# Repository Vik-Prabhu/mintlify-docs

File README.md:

# Smart Fault Detector

## Project Description

The **Smart-Fault-Detector** is a specialized diagnostic device engineered to detect actuator faults and failures in high-stakes systems like rockets and robotics. By monitoring the "pulse" of an actuator through electrical and mechanical sensors, it identifies anomalies before they lead to catastrophic system failure.

## 📘 Project Documentation & Deployment

### 🌐 Documentation (Mintlify)

This project uses **Mintlify** to host clean, modern documentation.

- Built using MDX
- Supports images, code blocks, and downloadable assets
- Automatically deployed on every update

**Documentation URL:**  https://teamrobomanipal-3a657712.mintlify.app/Introduction

````
To run docs locally:
npm install
mintlify dev
````

---

### 🚀 Backend Deployment (Render + Flask)

The backend is a **Flask + Socket.IO** server deployed on **Render**.

#### Why Render?

- Free tier support
- Simple GitHub integration
- Works well with Flask APIs
- Public endpoint accessible by ESP devices

#### Tech Stack

- Python
- Flask
- Flask-SocketIO
- Eventlet
- Render Web Service

#### Deployment Flow

1. Push code to GitHub
2. Create a **Web Service** on Render
3. Render installs dependencies from `requirements.txt`
4. App runs on a public HTTPS URL

 **Dashboard URL:** https://mintlify-docs-w26p.onrender.com

---

### 📡 ESP ↔ Server Communication

- ESP device sends data via HTTP / Socket.IO

- Flask server receives and processes data

- Real-time updates supported using WebSockets
- Designed for low-latency actuator/health monitoring

---

### 📂 Key Files

```text
.
├── Firmware            # Contains ESP32-C3 Code
├── PCB                 # KiCAD Design Files
```

```
.
├── docs.json             # Contains structured metadata for the project 
├── package-lock.json     # Auto-generated file for mintlify
```

```
Dashboard_src
├── server.py              # Webserver UI
├── health_model.py        # Predictive Algorithm
├── requirements.txt       # Python dependencies
```

---

### 🛠️ requirements.txt

```txt
flask
flask-socketio
eventlet
```

---

### ✅ Status

- [x] Backend deployed on Render
- [x] Documentation live on Mintlify
- [x] ESP integration working

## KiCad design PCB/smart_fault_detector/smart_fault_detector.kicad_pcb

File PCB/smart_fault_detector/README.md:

# Hardware-Hackathon-2.0
for hackathon

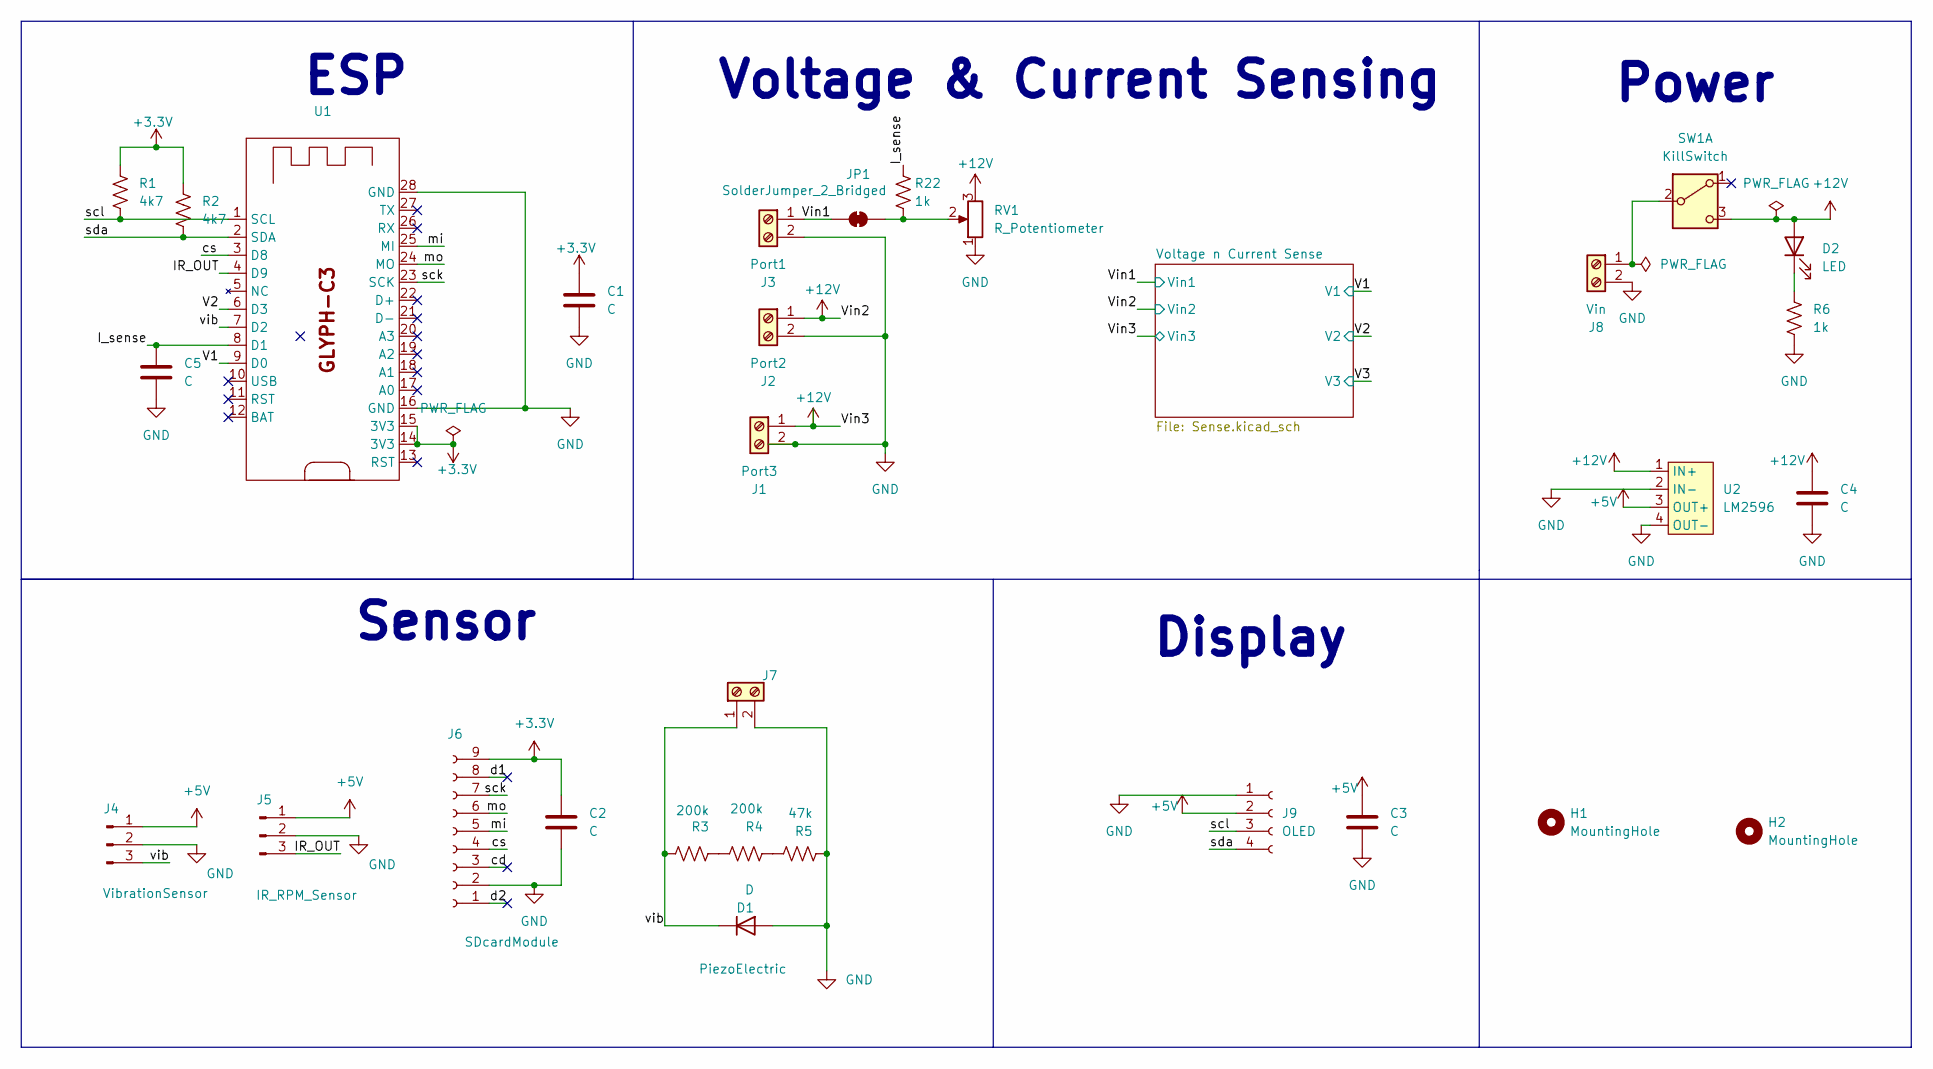
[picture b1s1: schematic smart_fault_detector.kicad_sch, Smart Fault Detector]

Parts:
C1, C3, C4, C5: C; C_1206_3216Metric
C2: C; C_0603_1608Metric_Pad1.08x0.95mm_HandSolder
D1: D; D_SMA_Handsoldering
D2: LED; LED_0603_1608Metric_Pad1.05x0.95mm_HandSolder
H1, H2: MountingHole; MountingHole_3.2mm_M3
J1: Port3; TerminalBlock_Phoenix_MKDS-1,5-2-5.08_1x02_P5.08mm_Horizont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
J2: Port2; TerminalBlock_Phoenix_MKDS-1,5-2-5.08_1x02_P5.08mm_Horizont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
J3: Port1; TerminalBlock_Phoenix_MKDS-1,5-2-5.08_1x02_P5.08mm_Horizont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
J4: VibrationSensor; PinSocket_1x03_P2.54mm_Vertical
J5: IR_RPM_Sensor; PinSocket_1x03_P2.54mm_Vertical
J6: SDcardModule; PinSocket_1x09_P2.54mm_Vertical
J7: PiezoElectric; TerminalBlock_Phoenix_MKDS-1,5-2-5.08_1x02_P5.08mm_Horizont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
J8: Vin; TerminalBlock_Phoenix_MKDS-1,5-2-5.08_1x02_P5.08mm_Horizont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
J9: OLED; PinSocket_1x04_P2.54mm_Vertical
JP1: SolderJumper_2_Bridged; SolderJumper-2_P1.3mm_Bridged_RoundedPad1.0x1.5mm
R1, R2: 4k7; R_0805_2012Metric_Pad1.20x1.40mm_HandSolder
R3, R4: 200k; R_0805_2012Metric_Pad1.20x1.40mm_HandSolder
R5: 47k; R_0805_2012Metric_Pad1.20x1.40mm_HandSolder
R6, R22: 1k; R_0805_2012Metric_Pad1.20x1.40mm_HandSolder
RV1: R_Potentiometer; Potentiometer_Alps_RK163_Single_Horizontal
SW1: KillSwitch; SW_TL2230EEF140
U1: GlyphC3
U2: LM2596; LM2596_Buck

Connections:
+3.3V: C1.1, C2.1, J6.9, R1.1, R2.1, U1.14 (3V3), U1.15 (3V3)
+5V: C3.1, J4.1, J5.1, J9.2, U2.3 (OUT+); also elsewhere on the board
+12V: C4.1, D2.2 (A), J1.1, J2.1, RV1.3, SW1.3 (C), U2.1 (IN+); also elsewhere on the board
/IR_OUT: J5.3, U1.4 (D9)
/I_sense: C5.1, R22.1, U1.8 (D1)
/V1: U1.9 (D0); also elsewhere on the board
/V2: U1.6 (D3); also elsewhere on the board
/Vin1: J3.1, JP1.1 (A); also elsewhere on the board
/cd: J6.3
/cs: J6.4, U1.3 (D8)
/d1: J6.8
/d2: J6.1
/mi: J6.5, U1.25 (MI)
/mo: J6.6, U1.24 (MO)
/sck: J6.7, U1.23 (SCK)
/scl: J9.3, R1.2, U1.1 (SCL)
/sda: J9.4, R2.2, U1.2 (SDA)
/vib: D1.1 (K), J4.3, J7.1, R3.1, U1.7 (D2)
GND: C1.2, C2.2, C3.2, C4.2, C5.2, D1.2 (A), J1.2, J2.2, J3.2, J4.2, J5.2, J6.2, J7.2, J8.2, J9.1, R5.2, R6.2, RV1.1, U1.16 (GND), U1.28 (GND), U2.2 (IN-), U2.4 (OUT-); also elsewhere on the board
unnamed: D2.1 (K), R6.1
unnamed: J8.1, SW1.2 (B)
unnamed: JP1.2 (B), R22.2, RV1.2
unnamed: R3.2, R4.1
unnamed: R4.2, R5.1

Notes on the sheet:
ESP
Sensor
Voltage & Current Sensing
Power
Display

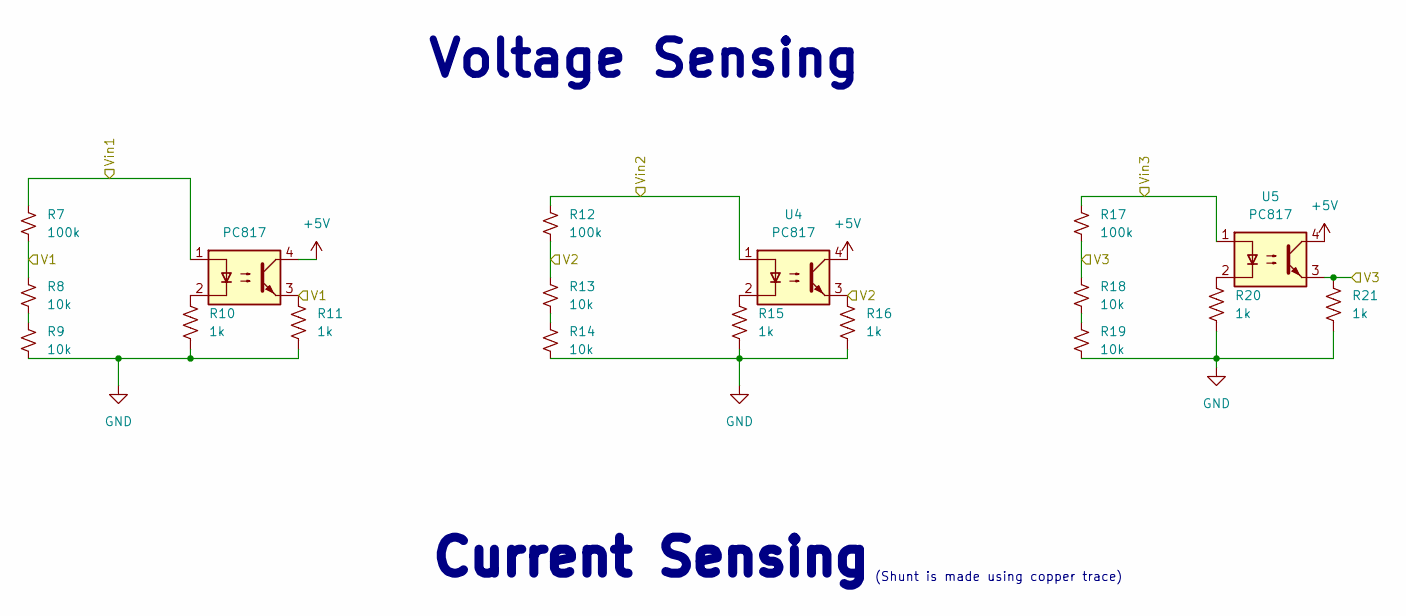
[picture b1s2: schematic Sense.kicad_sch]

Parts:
R7, R12, R17: 100k; R_0805_2012Metric_Pad1.20x1.40mm_HandSolder
R8, R9, R13, R14, R18, R19: 10k; R_0805_2012Metric_Pad1.20x1.40mm_HandSolder
R10, R11, R15, R16, R20, R21: 1k; R_0805_2012Metric_Pad1.20x1.40mm_HandSolder
U3, U4, U5: PC817; DIP-4_W7.62mm

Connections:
+5V: U3.4, U4.4, U5.4; also elsewhere on the board
+12V: R12.1, R17.1, U4.1, U5.1; also elsewhere on the board
/V1: R7.2, R8.1, R11.1, U3.3; also elsewhere on the board
/V2: R12.2, R13.1, R16.1, U4.3; also elsewhere on the board
/V3: R17.2, R18.1, R21.1, U5.3
/Vin1: R7.1, U3.1; also elsewhere on the board
GND: R9.2, R10.2, R11.2, R14.2, R15.2, R16.2, R19.2, R20.2, R21.2; also elsewhere on the board
unnamed: R8.2, R9.1
unnamed: R10.1, U3.2
unnamed: R13.2, R14.1
unnamed: R15.1, U4.2
unnamed: R18.2, R19.1
unnamed: R20.1, U5.2

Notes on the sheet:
(Shunt is made using copper trace)
Voltage Sensing
Current Sensing

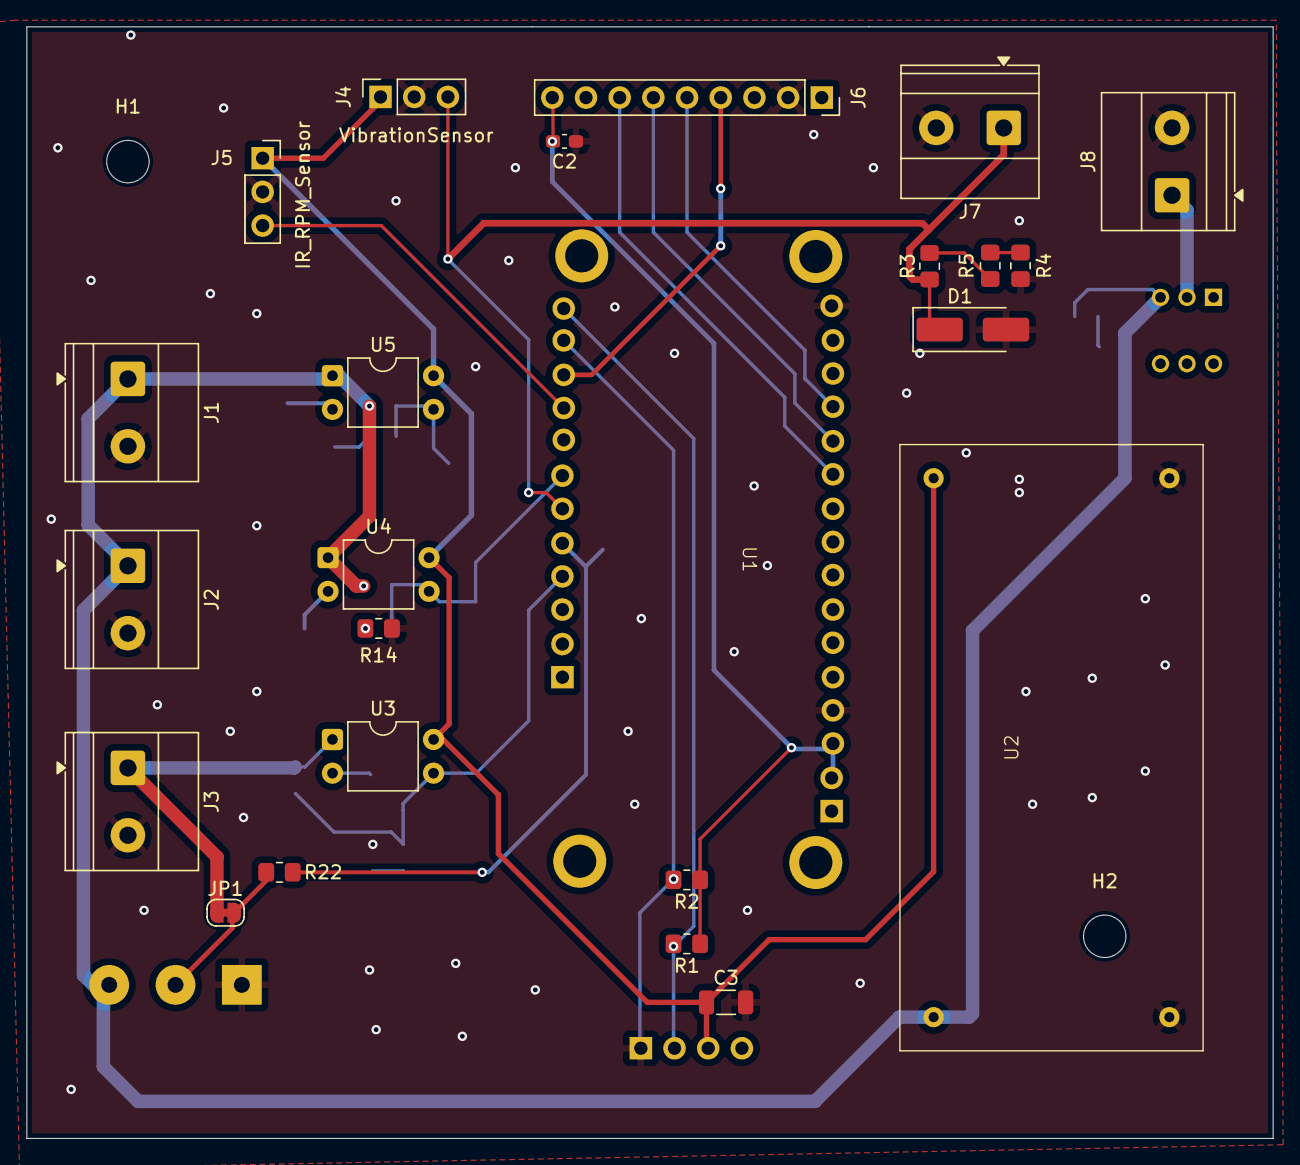
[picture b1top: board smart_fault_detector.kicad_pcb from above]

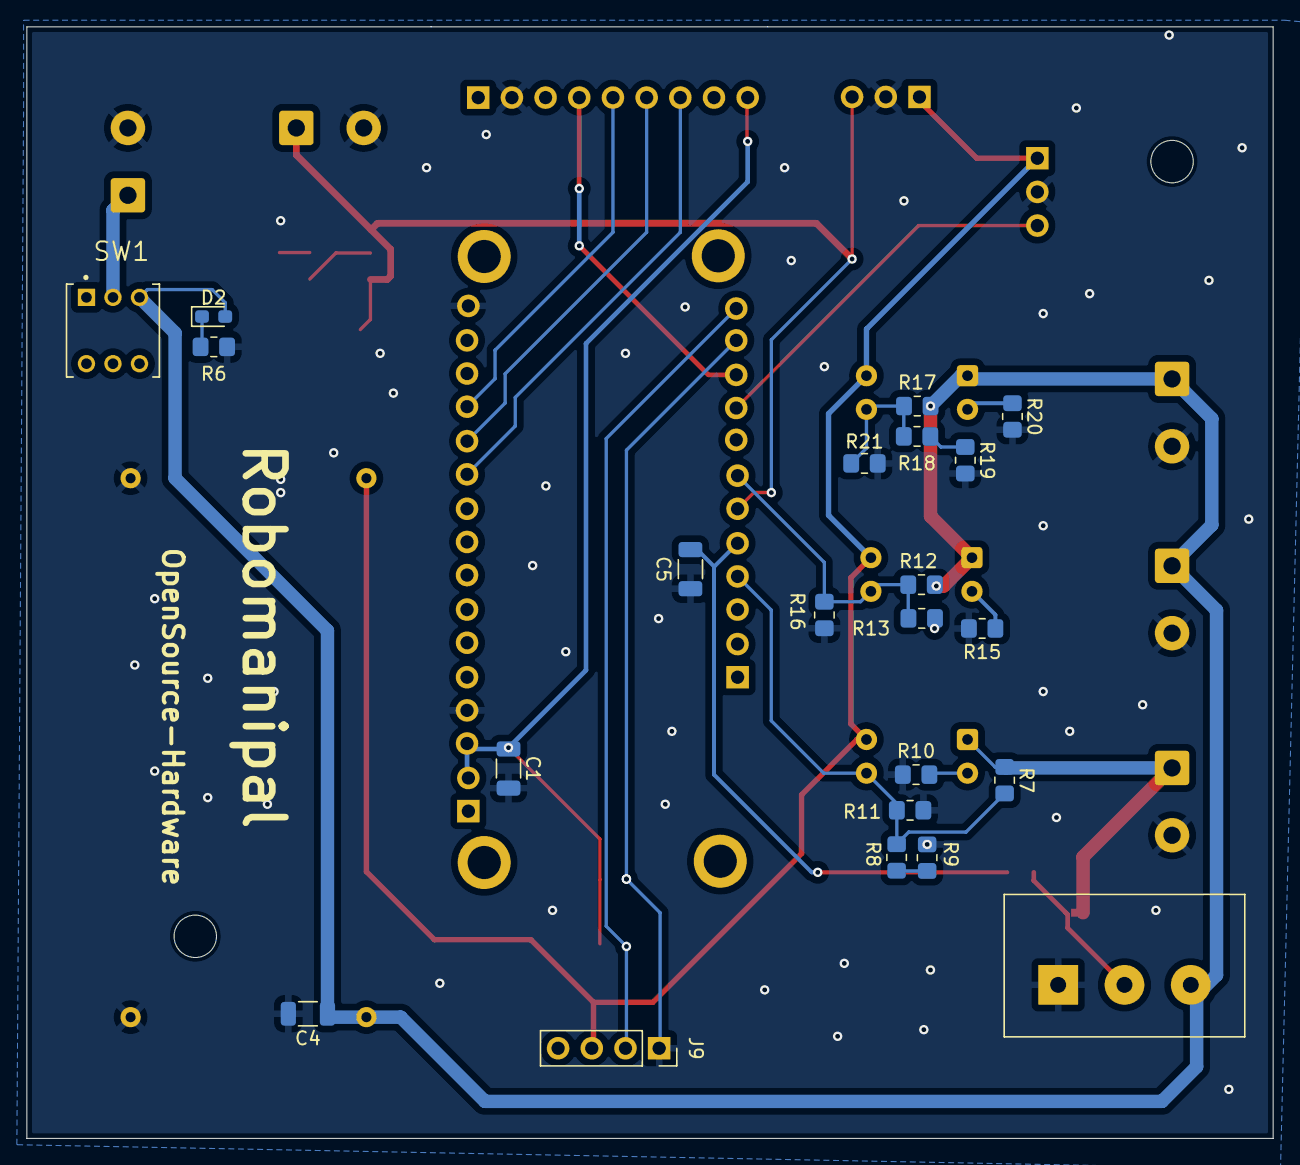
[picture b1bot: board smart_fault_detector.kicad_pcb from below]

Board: 2 copper layers, 94.0 x 83.8 mm, 48 parts (22 on the bottom side), 28 nets.

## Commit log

2025-12-20 restore
2025-12-20 hardware-doc-done
2025-12-21 added_status_server
2025-12-21 code doc done & intro updated
2025-12-21 dashboard & ML doc added
2025-12-21 added future scope
2025-12-22 hosted it lezgo
2025-12-22 Added Dev Container Folder
2025-12-22 Trying to host Dashboard
2025-12-22 added Dashboard_src
2025-12-22 deployed dashboard
2025-12-22 fixed dashboard button
2025-12-22 Enhance README with deployment and communication details
    Expanded project documentation to include detailed sections on backend deployment, ESP communication, and key files.
2025-12-23 combined PCB n Firmware
2025-12-23 minor changes
